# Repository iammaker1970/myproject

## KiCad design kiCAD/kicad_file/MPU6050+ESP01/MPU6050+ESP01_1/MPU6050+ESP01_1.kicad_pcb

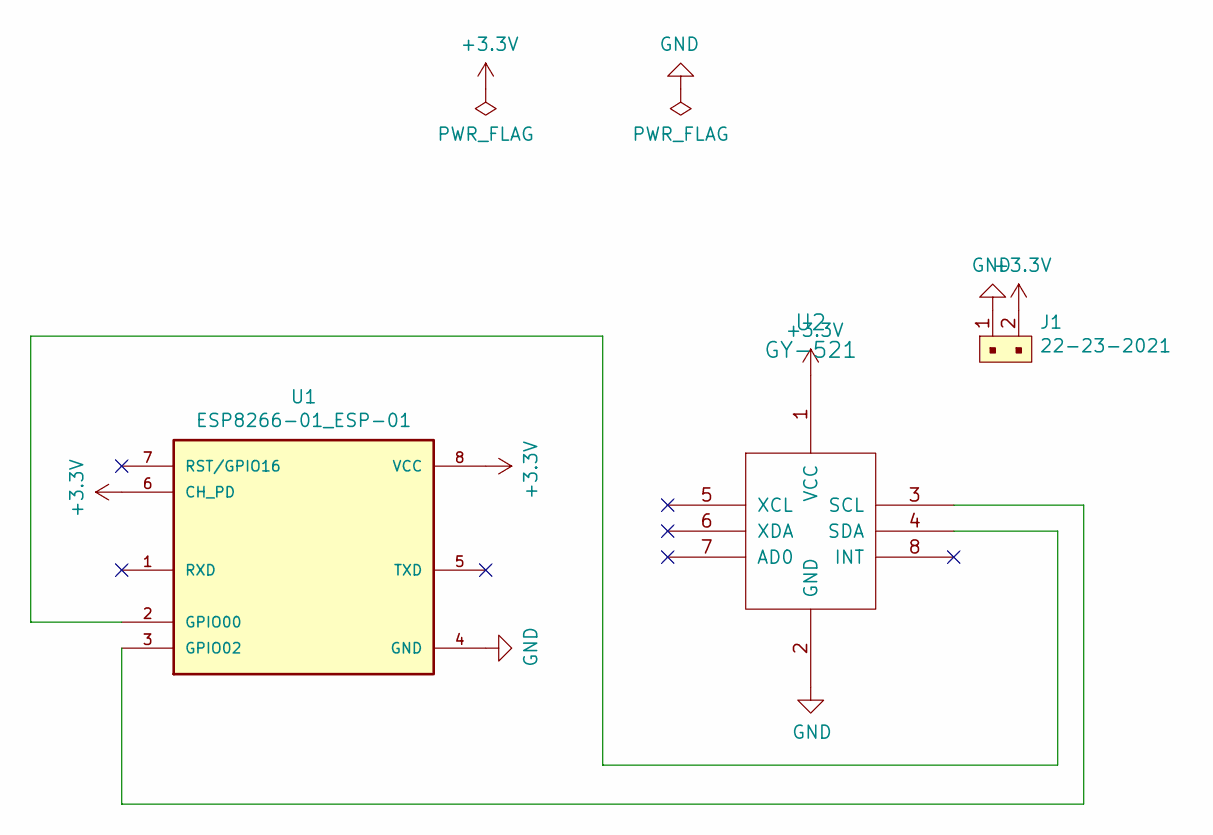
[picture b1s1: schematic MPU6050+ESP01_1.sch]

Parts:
J1: 22-23-2021; PinHeader_1x2_P2.54mm_Drill1.02mm; MPN 22-23-2021; Digi-Key_PN WM4200-ND
U1: ESP8266-01_ESP-01; ESP-01
U2: GY-521

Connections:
+3V3: J1.2, U1.6 (CH_PD), U1.8 (VCC), U2.1 (VCC)
GND: J1.1, U1.4 (GND), U2.2 (GND)
unnamed: U1.2 (GPIO00), U2.4 (SDA)
unnamed: U1.3 (GPIO02), U2.3 (SCL)

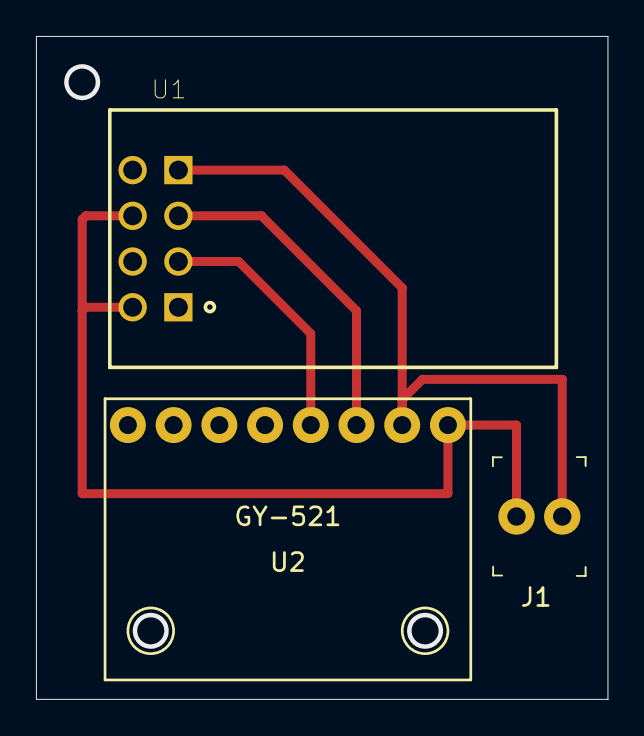
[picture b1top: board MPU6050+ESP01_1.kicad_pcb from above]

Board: 2 copper layers, 31.8 x 36.8 mm, 3 parts (0 on the bottom side), 4 nets.

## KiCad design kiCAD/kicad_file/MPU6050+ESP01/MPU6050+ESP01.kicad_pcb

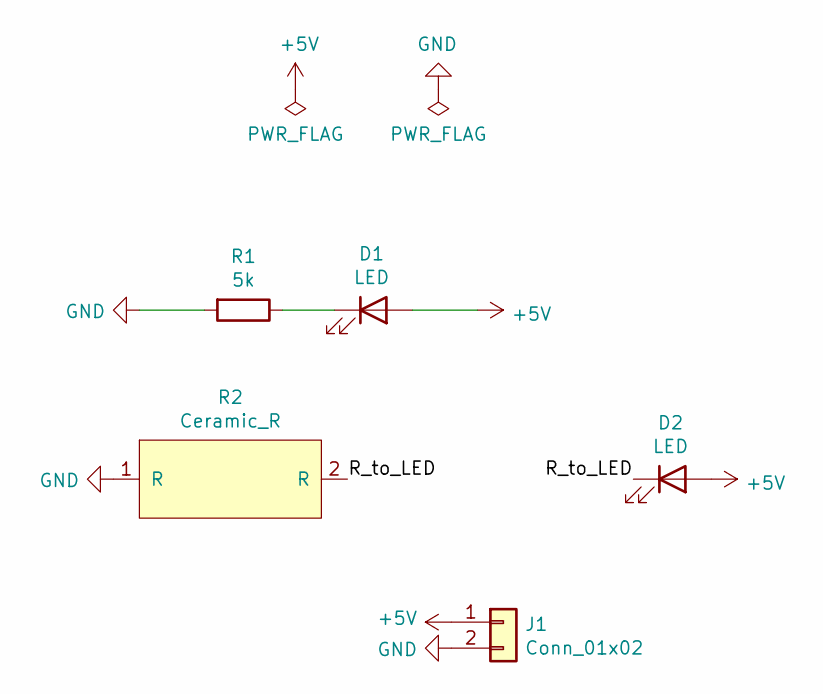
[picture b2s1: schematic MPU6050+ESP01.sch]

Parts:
D1, D2: LED; LED_D5.0mm
J1: Conn_01x02; PinSocket_1x02_P2.54mm_Vertical
R1: 5k; R_Axial_DIN0614_L14.3mm_D5.7mm_P25.40mm_Horizontal
R2: Ceramic_R

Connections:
+5V: D1.2 (A), D2.2 (A), J1.1
/R_to_LED: D2.1 (K), R2.2
GND: J1.2, R1.2, R2.1
unnamed: D1.1 (K), R1.1

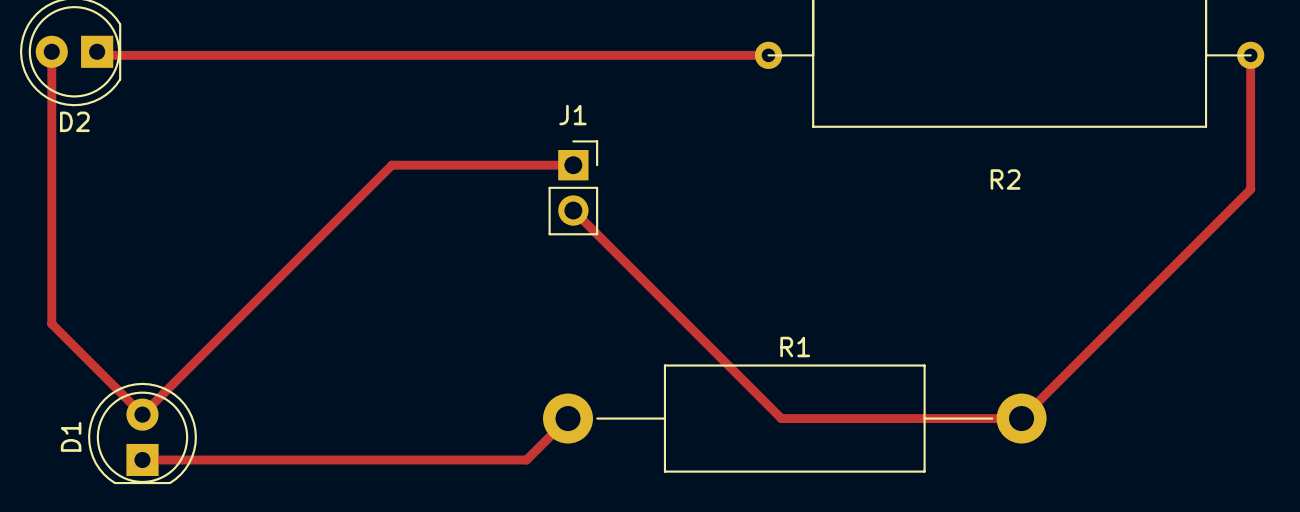
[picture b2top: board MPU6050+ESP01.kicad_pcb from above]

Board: 2 copper layers, 5 parts (0 on the bottom side), 4 nets.

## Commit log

2020-05-18 Add hello.txt
2020-09-17 new file
2020-10-12 add test.txt
2020-10-20 Add machine_project
2020-10-25 modify hello.txt
2020-10-29 node-red update
2020-10-30 ESP8266_reference
2020-11-01 code moduify
2020-11-02 ESP-01 kicad library
2020-11-27 20201127
2020-11-30 20201130
2020-12-02 20201202
2020-12-02 20201202_2
2020-12-04 20201204
2020-12-05 node-red backup
2020-12-05 ESP-cam in NODE-RED
2020-12-06 IP33_ALL_JSON
2020-12-07 ESP32_CAM_multiple clients
2020-12-09 20201210
2020-12-10 20201210-1
2020-12-11 20201212
2020-12-11 20201212-1
2020-12-16 20201216
2020-12-16 20201216-1
2020-12-16 20201217
2020-12-17 20201217-1
2020-12-17 20201217-2
2020-12-17 20201217-3
2020-12-17 20201218-1
2020-12-17 20201218-2
2020-12-18 20201218-3
2020-12-19 20201219
2020-12-19 20201219-1
2020-12-19 20201219-2
2020-12-19 20201220
2020-12-24 20201224
2020-12-26 20201226
2020-12-28 20201228
2021-01-02 20210102
2021-01-06 20210105
2021-01-06 20210106
2021-02-15 20210215
2021-03-02 20210302
2021-03-04 20210304
